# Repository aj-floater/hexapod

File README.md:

# Hexapod Robot Public Repository

## Introduction

This repository contains the public engineering artifacts for a six-legged robot project. It combines embedded firmware for RP2040-based control experiments, host-side tooling for communicating with and visualizing device state, a C++ simulation/editor shell, hardware design files, and supporting media used during development.

The public repository is organised to let a technically competent reader inspect the control stack, reproduce the host tooling, build the current simulation executable, and review the mechanical and electronics design files. It is intended as the software and hardware workspace for the project rather than a polished end-user product.

## Contextual Overview

The project is split into four main layers:

```text
hardware/ CAD and PCB assets
    ->
firmware/ RP2040 targets implementing control loops and devlink endpoints
    <-UART/devlink->
tools/devlink_dashboard/ Python host tooling for monitor, replay, commands, and GUI

software/simulation/ C++ editor-style sandbox for kinematic and UI experiments
media/ public images and videos used to illustrate development results
```

In practice, the most direct public workflow is to run a firmware target on an RP2040 board, connect it over the current devlink serial path, and inspect or record the device stream with `devlink-dashboard`.

## Repository Layout

- `firmware/`: RP2040 firmware targets, shared support code, and experimental control programs
- `tools/devlink_dashboard/`: Python package for serial monitoring, command dispatch, recording, replay, and the desktop GUI
- `software/simulation/`: Magnum-based C++ simulation/editor shell with vendored third-party dependencies
- `hardware/`: FreeCAD assemblies, KiCad projects, and board-level hardware assets
- `media/`: images and videos that illustrate assembly, calibration, and control behaviour

## Installation Instructions

### 1. Clone the repository

```bash
git clone git@github.com:aj-floater/hexapod.git
cd hexapod
```

### 2. Host tooling prerequisites

Required for `tools/devlink_dashboard/`:

- Python `>=3.11`
- `pip`
- serial support via `pyserial`
- GUI support via `PySide6` and `pyqtgraph` when using the desktop dashboard

Install the package from the repository root:

```bash
python3 -m pip install -e './tools/devlink_dashboard[gui]'
```

If you only need parser, replay, or non-GUI workflows, install the lighter serial extra instead:

```bash
python3 -m pip install -e './tools/devlink_dashboard[serial]'
```

### 3. Simulation prerequisites

Required for `software/simulation/`:

- CMake `>=3.24`
- a C++17 compiler
- a desktop OpenGL-capable environment

The simulation currently vendors its external dependencies under `software/simulation/third_party/`, so no separate package manager is required for Corrade, Magnum, SDL, ImGui, or ImGuizmo in the default workflow.

### 4. Firmware prerequisites

Required for `firmware/` work:

- Raspberry Pi Pico SDK / RP2040 toolchain
- CMake and a C/C++ compiler
- an SWD probe such as Pico Probe or a compatible CMSIS-DAP device for flashing and debugging
- UART wiring when using the current devlink path

Board-specific notes in `firmware/board.md` currently assume:

- `GP4 -> host RX`
- `GP3 -> host TX`
- shared `GND`

### 5. Hardware prerequisites

Required for `hardware/` inspection and editing:

- FreeCAD for `.FCStd` assemblies and parts
- KiCad for PCB and schematic projects

## How to Run the Software

### Host dashboard

Launch the desktop dashboard against a live serial device:

```bash
devlink-dashboard gui --port /dev/ttyACM0 --record session.jsonl
```

Other useful host workflows:

```bash
devlink-dashboard monitor --port /dev/ttyACM0 --record session.jsonl
devlink-dashboard replay session.jsonl
```

### Simulation

Configure, build, and run the current simulation shell:

```bash
cmake -S software/simulation -B software/simulation/build
cmake --build software/simulation/build
./software/simulation/build/bin/hexapod-simulation
```

### Firmware example

One simple public firmware workflow is the RP2040 blink/debug example:

```bash
cd firmware/blink_any_copy
make build
make flash
```

More advanced control targets live under `firmware/control_testing/`, `firmware/basic_control_testing/`, and related subdirectories.

## Technical Details

- The host-device protocol work is centered on `devlink`, with typed messages, NDJSON logging/replay, and capability-driven host state reconstruction in `tools/devlink_dashboard/`.
- Current firmware work targets RP2040 boards and uses a UART-based devlink transport. The public board notes document the active wiring assumptions and shared RX helper usage.
- The simulation executable is an editor-style sandbox rather than a full robot simulator. It currently focuses on a dockable viewport, scene hierarchy, gizmo manipulation, and persistence while replay and joint-domain integration remain future work.
- The simulation build intentionally vendors its major third-party dependencies under `software/simulation/third_party/` and pins them through the local CMake configuration.
- Hardware assets are maintained directly in native design formats so the repository doubles as a source tree for mechanical and PCB iteration, not only as an exported artifact store.

## Known Issues and Future Improvements

- The repository is large because it includes vendored C++ dependencies, CAD files, PCB assets, images, and captured telemetry recordings.
- Some tracked recordings and generated artifacts are large enough to trigger GitHub large-file warnings and may need Git LFS or curation later.
- The simulation scope is still limited to the editor/bootstrap phase; full replay, model import, and complete multi-joint behaviour are not finished.
- Firmware workflows are target-specific and assume local toolchain, probe, and serial environment setup rather than a single turnkey build.
- Hardware and software subsystems are evolving in parallel, so interfaces and assumptions may continue to change as the robot architecture matures.

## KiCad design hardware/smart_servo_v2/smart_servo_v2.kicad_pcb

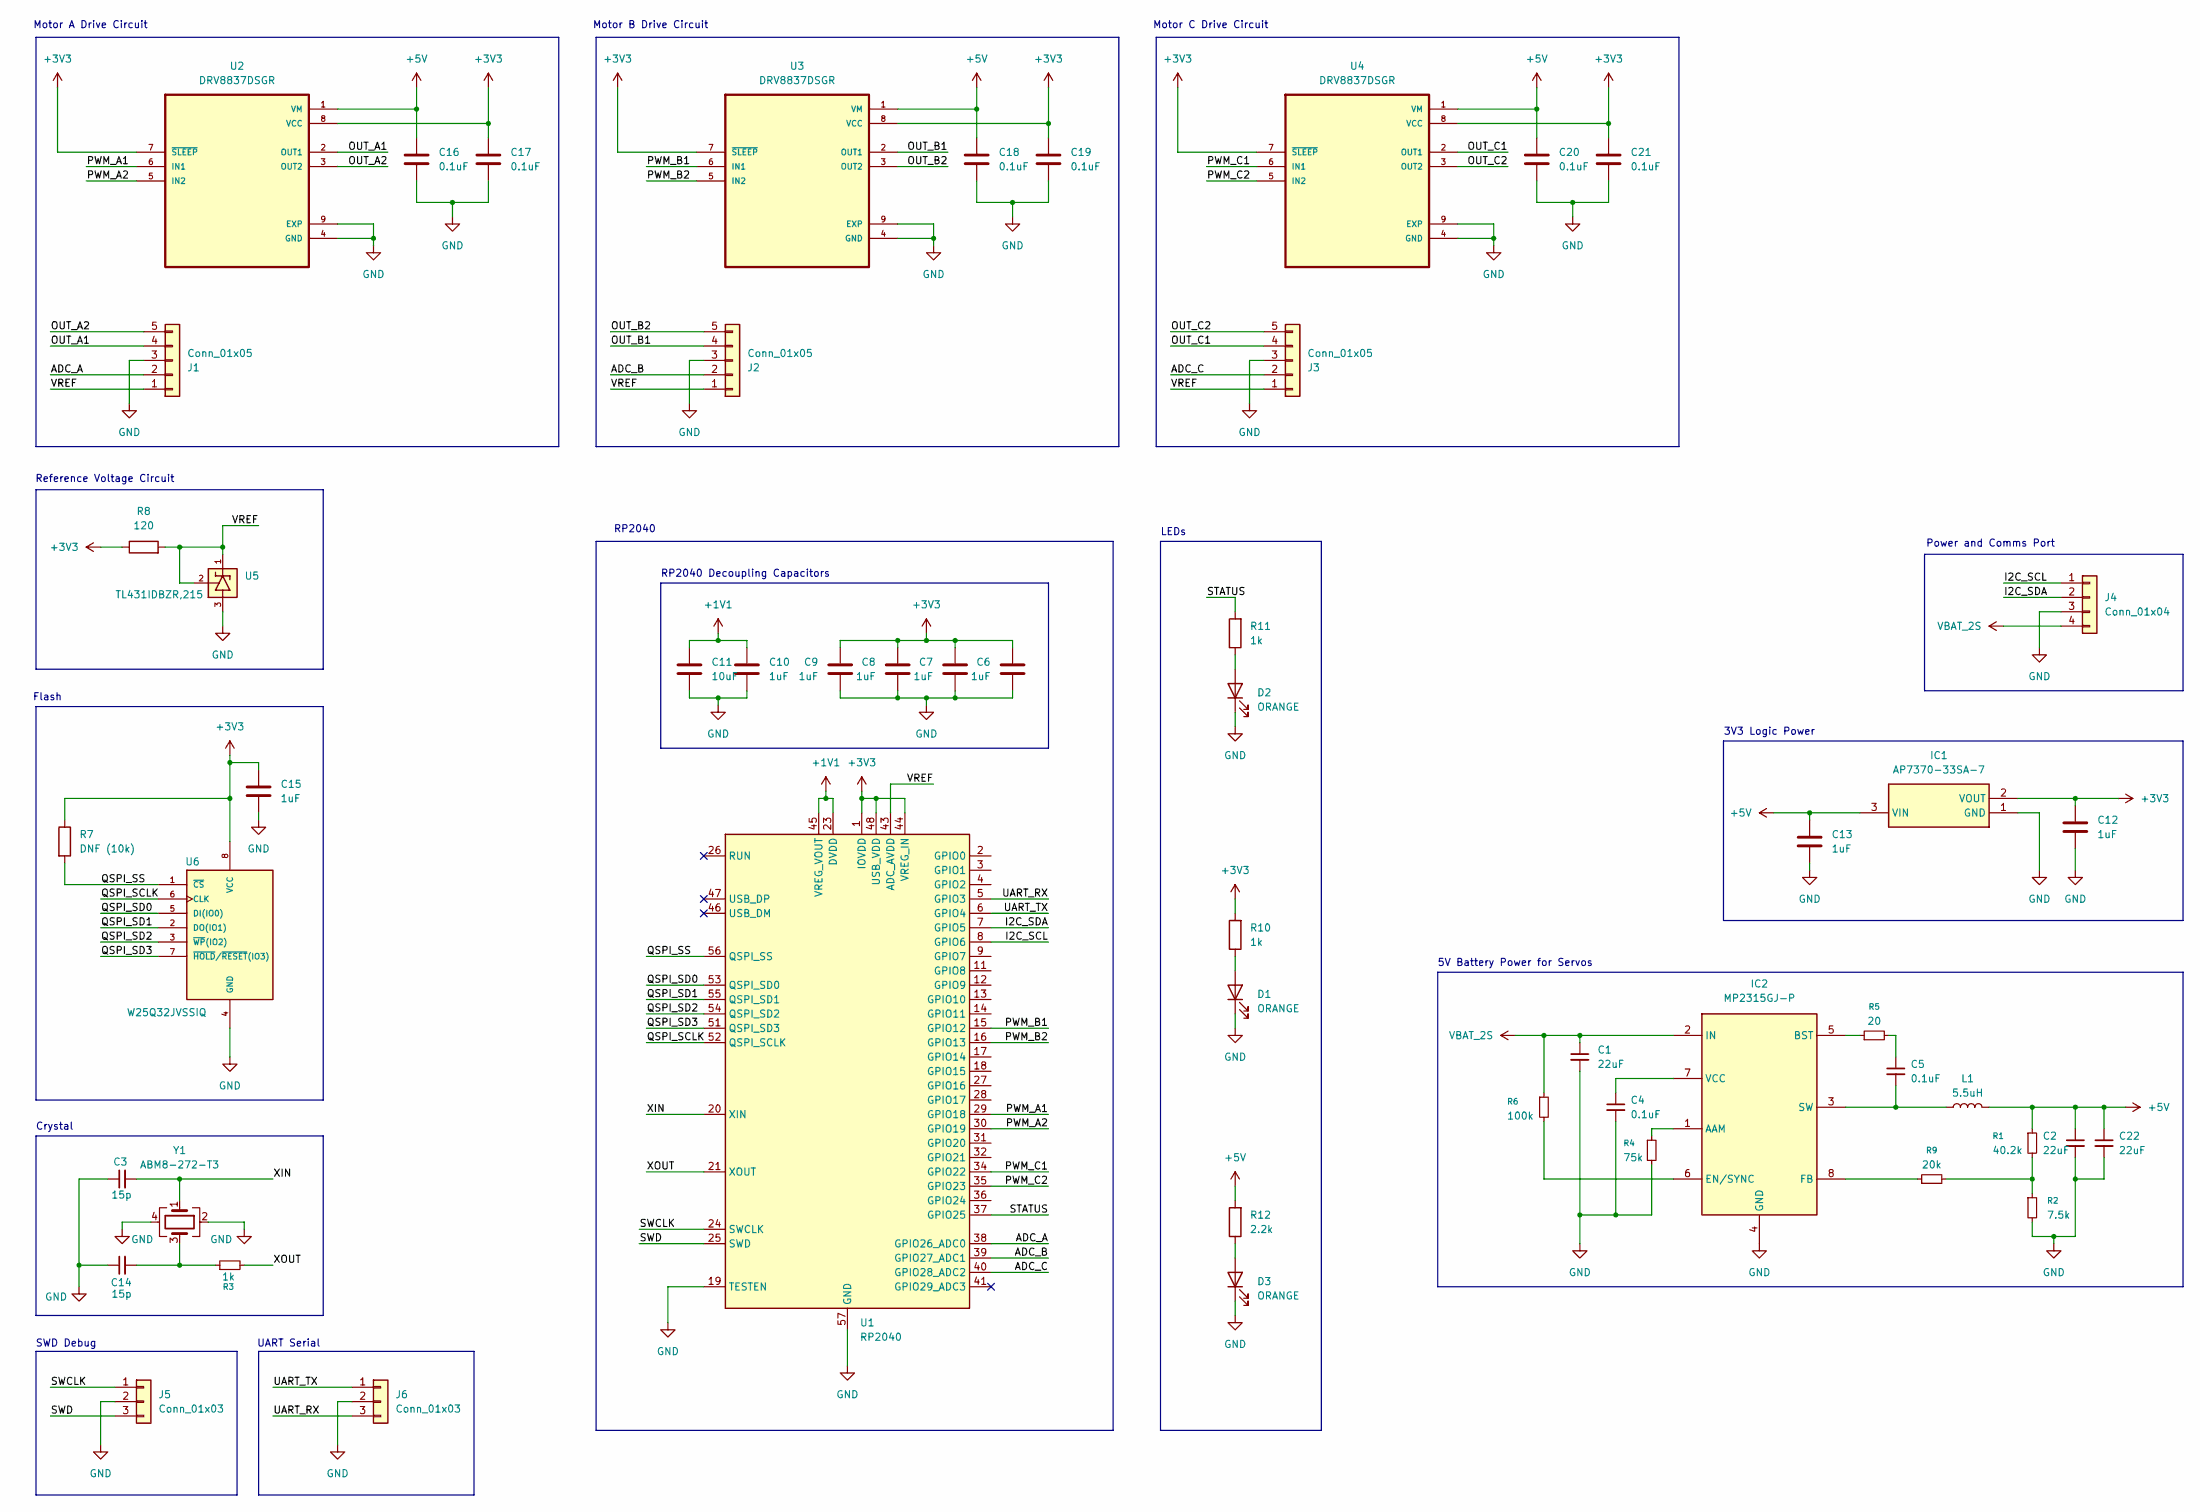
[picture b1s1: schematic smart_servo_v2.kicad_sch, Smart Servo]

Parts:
C1, C2, C22: 22uF; C_0603_1608Metric
C3, C14: 15p; C_0603_1608Metric
C4, C5, C16, C17, C18, C19, C20, C21: 0.1uF; C_0603_1608Metric
C6, C7, C8, C9, C10, C12, C13, C15: 1uF; C_0603_1608Metric
C11: 10uF; C_0603_1608Metric
D1, D2, D3: ORANGE; LED_0603_1608Metric; Manufacturer_Part_Number LO Q976.01
IC1: AP7370-33SA-7; SOT96P240X110-3N; Manufacturer_Part_Number AP7370-33SA-7
IC2: MP2315GJ-P; SOT65P280X100-8N; Manufacturer_Part_Number MP2315GJ-P
J1, J2, J3: Conn_01x05; JST_PH_B5B-PH-K_1x05_P2.00mm_Vertical
J4: Conn_01x04; JST_XH_B4B-XH-A_1x04_P2.50mm_Vertical
J5, J6: Conn_01x03; JST_PH_B3B-PH-K_1x03_P2.00mm_Vertical
L1: 5.5uH; L_Bourns_SRP7028A_7.3x6.6mm; Manufacturer_Part_Number SRP7028A-4R7M
R1: 40.2k; R_0805_2012Metric
R2: 7.5k; R_0603_1608Metric
R3, R10, R11: 1k; R_0603_1608Metric
R4: 75k; R_0805_2012Metric
R5: 20; R_0603_1608Metric
R6: 100k; R_0805_2012Metric
R7: DNF (10k); R_0805_2012Metric
R8: 120; R_0603_1608Metric
R9: 20k; R_0603_1608Metric
R12: 2.2k; R_0603_1608Metric
U1: RP2040; QFN-56-1EP_7x7mm_P0.4mm_EP3.2x3.2mm; Manufacturer_Part_Number RP2040CT
U2, U3, U4: DRV8837DSGR; SON50P200X200X80-9N; Manufacturer_Part_Number DRV8837DSGR
U5: TL431IDBZR,215; SOT95P255X145-3N; PARTREV P
U6: W25Q32JVSSIQ; SOIC127P790X216-8N; M_PART_NUMBER W25QXX
Y1: ABM8-272-T3; ABM8272T3; Manufacturer_Part_Number ABM8-272-T3

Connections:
+1V1: C10.1, C11.1, U1.23 (DVDD), U1.45 (VREG_VOUT), U1.50 (DVDD)
+3V3: C6.1, C7.1, C8.1, C9.1, C12.1, C15.1, C17.1, C19.1, C21.1, IC1.2 (VOUT), R7.1, R8.1, R10.2, U1.1 (IOVDD), U1.10 (IOVDD), U1.22 (IOVDD), U1.33 (IOVDD), U1.42 (IOVDD), U1.44 (VREG_IN), U1.48 (USB_VDD), U1.49 (IOVDD), U2.7 (~SLEEP), U2.8 (VCC), U3.7 (~SLEEP), U3.8 (VCC), U4.7 (~SLEEP), U4.8 (VCC), U6.8 (VCC)
+5V: C2.1, C13.1, C16.1, C18.1, C20.1, C22.1, IC1.3 (VIN), L1.2, R1.1, R12.2, U2.1 (VM), U3.1 (VM), U4.1 (VM)
/ADC_A: J1.2, U1.38 (GPIO26_ADC0)
/ADC_B: J2.2, U1.39 (GPIO27_ADC1)
/ADC_C: J3.2, U1.40 (GPIO28_ADC2)
/I2C_SCL: J4.1, U1.8 (GPIO6)
/I2C_SDA: J4.2, U1.7 (GPIO5)
/OUT_A1: J1.4, U2.2 (OUT1)
/OUT_A2: J1.5, U2.3 (OUT2)
/OUT_B1: J2.4, U3.2 (OUT1)
/OUT_B2: J2.5, U3.3 (OUT2)
/OUT_C1: J3.4, U4.2 (OUT1)
/OUT_C2: J3.5, U4.3 (OUT2)
/PWM_A1: U1.29 (GPIO18), U2.6 (IN1)
/PWM_A2: U1.30 (GPIO19), U2.5 (IN2)
/PWM_B1: U1.15 (GPIO12), U3.6 (IN1)
/PWM_B2: U1.16 (GPIO13), U3.5 (IN2)
/PWM_C1: U1.34 (GPIO22), U4.6 (IN1)
/PWM_C2: U1.35 (GPIO23), U4.5 (IN2)
/QSPI_SCLK: U1.52 (QSPI_SCLK), U6.6 (CLK)
/QSPI_SD0: U1.53 (QSPI_SD0), U6.5 (DI(IO0))
/QSPI_SD1: U1.55 (QSPI_SD1), U6.2 (DO(IO1))
/QSPI_SD2: U1.54 (QSPI_SD2), U6.3 (~WP(IO2))
/QSPI_SD3: U1.51 (QSPI_SD3), U6.7 (~HOLD/~RESET(IO3))
/QSPI_SS: R7.2, U1.56 (QSPI_SS), U6.1 (~CS)
/STATUS: R11.2, U1.37 (GPIO25)
/SWCLK: J5.1, U1.24 (SWCLK)
/SWD: J5.3, U1.25 (SWD)
/UART_RX: J6.3, U1.5 (GPIO3)
/UART_TX: J6.1, U1.6 (GPIO4)
/VREF: J1.1, J2.1, J3.1, R8.2, U1.43 (ADC_AVDD), U5.1, U5.2
/XIN: C3.2, U1.20 (XIN), Y1.1
/XOUT: R3.2, U1.21 (XOUT)
GND: C1.2, C2.2, C3.1, C4.2, C6.2, C7.2, C8.2, C9.2, C10.2, C11.2, C12.2, C13.2, C14.1, C15.2, C16.2, C17.2, C18.2, C19.2, C20.2, C21.2, C22.2, D1.1 (K), D2.1 (K), D3.1 (K), IC1.1 (GND), IC2.4 (GND), J1.3, J2.3, J3.3, J4.3, J5.2, J6.2, R2.2, R4.2, U1.19 (TESTEN), U1.57 (GND), U2.4 (GND), U2.9 (EXP), U3.4 (GND), U3.9 (EXP), U4.4 (GND), U4.9 (EXP), U5.3, U6.4 (GND), Y1.2, Y1.4
unnamed: C5.1, R5.2
unnamed: C14.2, R3.1, Y1.3
unnamed: D1.2 (A), R10.1
unnamed: D2.2 (A), R11.1
unnamed: D3.2 (A), R12.1
unnamed: IC2.1 (AAM), R4.1
unnamed: IC2.5 (BST), R5.1
unnamed: IC2.6 (EN/SYNC), R6.2
unnamed: IC2.8 (FB), R9.1
unnamed: C5.2, IC2.3 (SW), L1.1
unnamed: C4.1, IC2.7 (VCC)
unnamed: R1.2, R2.1, R9.2
VBAT_2S: C1.1, IC2.2 (IN), J4.4, R6.1

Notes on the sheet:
5V Battery Power for Servos
Motor B Drive Circuit
Motor C Drive Circuit
Motor A Drive Circuit
UART Serial
LEDs
Crystal
Flash
Reference Voltage Circuit
RP2040
Power and Comms Port
SWD Debug
RP2040 Decoupling Capacitors
3V3 Logic Power

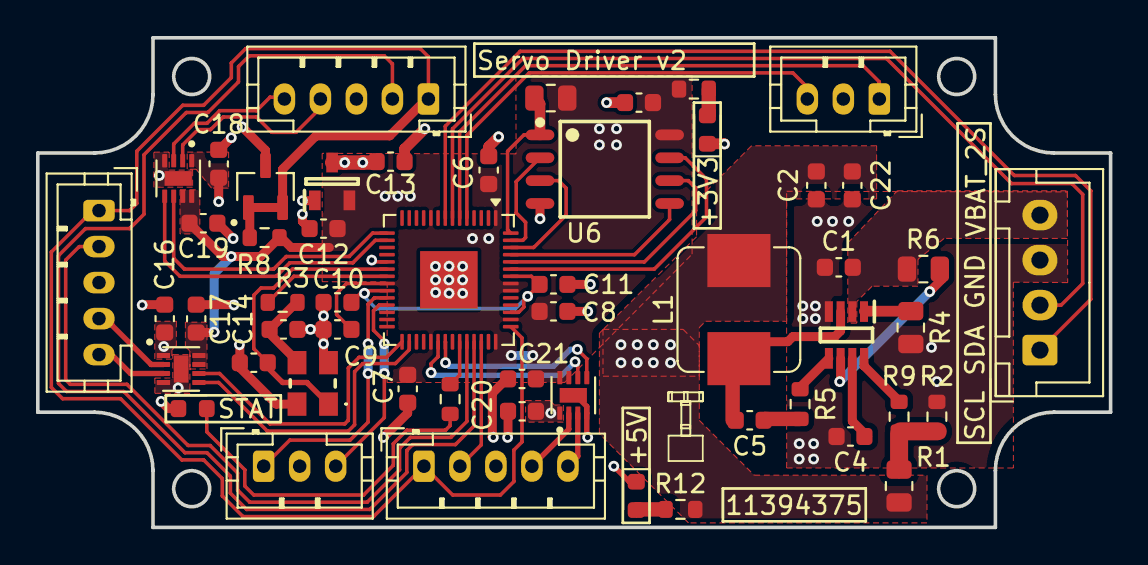
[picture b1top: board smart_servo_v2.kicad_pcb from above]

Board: 2 copper layers, 59.6 x 27.2 mm, 53 parts (0 on the bottom side), 48 nets.

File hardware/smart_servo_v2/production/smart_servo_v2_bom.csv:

Designator,Footprint,Quantity,Value,LCSC Part #
"C1, C2, C22",0603,3,22uF,
"C10, C12, C13, C15, C6, C7, C8, C9",0603,8,1uF,
C11,0603,1,10uF,
"C14, C3",0603,2,15p,
"C16, C17, C18, C19, C20, C21, C4, C5",0603,8,0.1uF,
"D1, D2, D3",0603,3,ORANGE,
IC1,SOT96P240X110-3N,1,AP7370-33SA-7,
IC2,SOT65P280X100-8N,1,MP2315GJ-P,
"J1, J2, J3",JST_PH_B5B-PH-K_1x05_P2.00mm_Vertical,3,Conn_01x05,
J4,JST_XH_B4B-XH-A_1x04_P2.50mm_Vertical,1,Conn_01x04,
"J5, J6",JST_PH_B3B-PH-K_1x03_P2.00mm_Vertical,2,Conn_01x03,
L1,L_Bourns_SRP7028A_7.3x6.6mm,1,5.5uH,
R1,0805,1,40.2k,
"R10, R11, R3",0603,3,1k,
R12,0603,1,2.2k,
R2,0603,1,7.5k,
R4,0805,1,75k,
R5,0603,1,20,
R6,0805,1,100k,
R7,0805,1,DNF (10k),
R8,0603,1,120,
R9,0603,1,20k,
U1,QFN-56-1EP_7x7mm_P0.4mm_EP3.2x3.2mm,1,RP2040,
"U2, U3, U4",SON50P200X200X80-9N,3,DRV8837DSGR,
U5,SOT95P255X145-3N,1,"TL431IDBZR,215",
U6,SOIC127P790X216-8N,1,W25Q32JVSSIQ,
Y1,ABM8272T3,1,ABM8-272-T3,

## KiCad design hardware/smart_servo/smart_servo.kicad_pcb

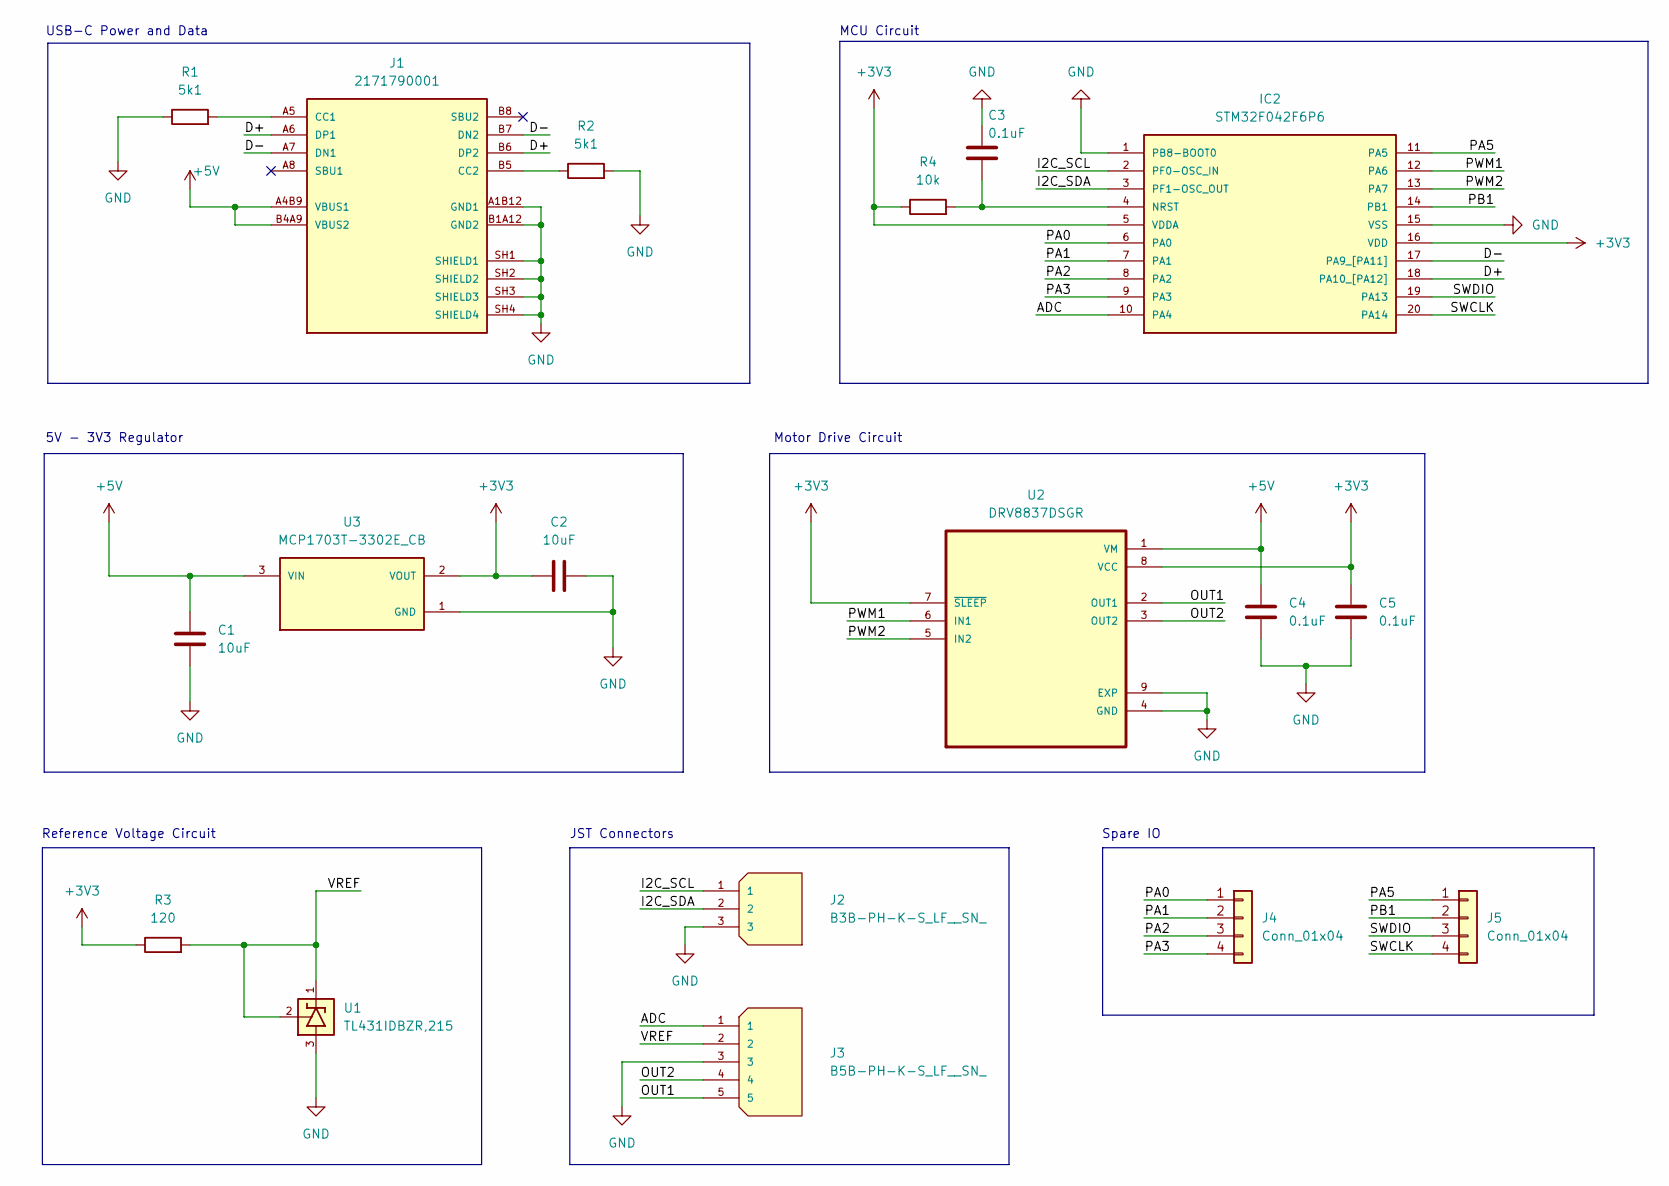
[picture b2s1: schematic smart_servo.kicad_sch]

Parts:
C1, C2: 10uF; C_0805_2012Metric
C3, C4, C5: 0.1uF; C_0402_1005Metric
IC2: STM32F042F6P6; SOP65P640X120-20N; MOUSER_PART_NUMBER 511-STM32F042F6P6
J1: 2171790001; MOLEX_2171790001; PARTREV A1
J2: B3B-PH-K-S_LF__SN_; JST_B3B-PH-K-S_LF__SN_
J3: B5B-PH-K-S_LF__SN_; JST_B5B-PH-K-S_LF__SN_
J4: Conn_01x04; PinSocket_1x04_P2.54mm_Vertical
J5: Conn_01x04; PinHeader_1x04_P2.54mm_Vertical
R1, R2: 5k1; R_0603_1608Metric
R3: 120; R_0402_1005Metric
R4: 10k; R_0402_1005Metric
U1: TL431IDBZR,215; SOT95P255X145-3N; PARTREV P
U2: DRV8837DSGR; SON50P200X200X80-9N
U3: MCP1703T-3302E_CB; SOT95P255X145-3N; PARTREV F

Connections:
+3V3: C2.2, C5.1, IC2.5 (VDDA), IC2.16 (VDD), R3.1, R4.1, U2.7 (~SLEEP), U2.8 (VCC), U3.2 (VOUT)
+5V: C1.1, C4.1, J1.A4B9 (VBUS1), J1.B4A9 (VBUS2), U2.1 (VM), U3.3 (VIN)
/ADC: IC2.10 (PA4), J3.1
/D+: IC2.18 (PA10_[PA12]), J1.A6 (DP1), J1.B6 (DP2)
/D-: IC2.17 (PA9_[PA11]), J1.A7 (DN1), J1.B7 (DN2)
/I2C_SCL: IC2.2 (PF0-OSC_IN), J2.1
/I2C_SDA: IC2.3 (PF1-OSC_OUT), J2.2
/OUT1: J3.5, U2.2 (OUT1)
/OUT2: J3.4, U2.3 (OUT2)
/PA0: IC2.6 (PA0), J4.1
/PA1: IC2.7 (PA1), J4.2
/PA2: IC2.8 (PA2), J4.3
/PA3: IC2.9 (PA3), J4.4
/PA5: IC2.11 (PA5), J5.1
/PB1: IC2.14 (PB1), J5.2
/PWM1: IC2.12 (PA6), U2.6 (IN1)
/PWM2: IC2.13 (PA7), U2.5 (IN2)
/SWCLK: IC2.20 (PA14), J5.4
/SWDIO: IC2.19 (PA13), J5.3
/VREF: J3.2, R3.2, U1.1, U1.2
GND: C1.2, C2.1, C3.1, C4.2, C5.2, IC2.1 (PB8-BOOT0), IC2.15 (VSS), J1.A1B12 (GND1), J1.B1A12 (GND2), J1.SH1 (SHIELD1), J1.SH2 (SHIELD2), J1.SH3 (SHIELD3), J1.SH4 (SHIELD4), J2.3, J3.3, R1.1, R2.2, U1.3, U2.4 (GND), U2.9 (EXP), U3.1 (GND)
unnamed: C3.2, IC2.4 (NRST), R4.2
unnamed: J1.A5 (CC1), R1.2
unnamed: J1.B5 (CC2), R2.1

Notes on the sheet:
USB-C Power and Data
Reference Voltage Circuit
Spare IO
MCU Circuit
Motor Drive Circuit
5V - 3V3 Regulator
JST Connectors

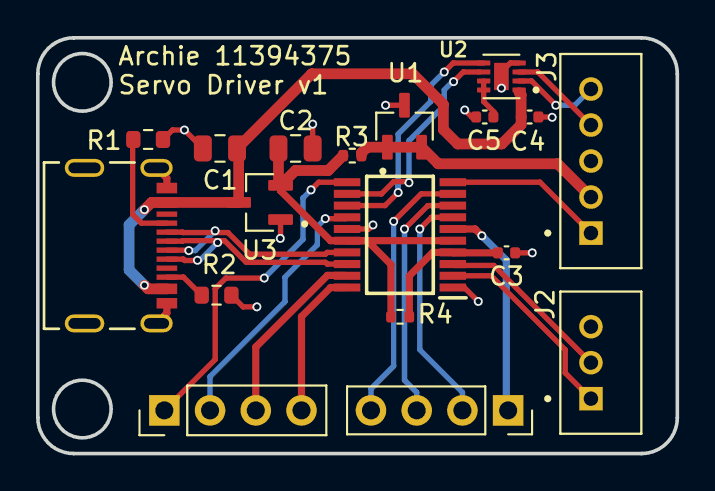
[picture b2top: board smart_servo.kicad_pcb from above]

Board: 2 copper layers, 35.5 x 23.1 mm, 18 parts (0 on the bottom side), 24 nets.

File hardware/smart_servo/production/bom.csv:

Designator,Footprint,Quantity,Value,LCSC Part #
"C1, C2",0805,2,10uF,
"C3, C4, C5",0402,3,0.1uF,
IC2,SOP65P640X120-20N,1,STM32F042F6P6,
J1,MOLEX_2171790001,1,2171790001,
J2,JST_B3B-PH-K-S_LF__SN_,1,B3B-PH-K-S_LF__SN_,
J3,JST_B5B-PH-K-S_LF__SN_,1,B5B-PH-K-S_LF__SN_,
J4,PinSocket_1x04_P2.54mm_Vertical,1,Conn_01x04,
J5,PinHeader_1x04_P2.54mm_Vertical,1,Conn_01x04,
"R1, R2",0603,2,5k1,
R3,0402,1,120,
R4,0402,1,10k,
U1,SOT95P255X145-3N,1,"TL431IDBZR,215",
U2,SON50P200X200X80-9N,1,DRV8837DSGR,
U3,SOT95P255X145-3N,1,MCP1703T-3302E_CB,

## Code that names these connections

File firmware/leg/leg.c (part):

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
static void init_adc_bank(AdcBank *bank) {
    adc_pot_system_init();
    adc_pot_init(&bank->a, "adc_a", LEG_POT_A_GPIO);
    adc_pot_init(&bank->b, "adc_b", LEG_POT_B_GPIO);
    adc_pot_init(&bank->c, "adc_c", LEG_POT_C_GPIO);
}

static void init_motor_bank(MotorBank *bank) {
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
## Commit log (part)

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2025-10-16 Add .gitignore for LaTeX auxiliary files
2025-10-16 repository for research and development of a six‑legged robot (simulation, firmware, hardware design and documentation).
2025-10-17 - project outline gantt chart good
2025-10-17 - completed project outline and uploaded
2025-10-17 - added the risk assessment
2026-02-13 Add blink_any project with GPIO25 blink firmware
2026-02-13 Add VS Code project settings for blink_any
2026-02-13 Add KiCad ESP32 demo project assets
2026-02-13 Add RP2040 minimal r2 hardware project
2026-02-13 Add rc-transmitter hardware project
2026-02-13 Add smart_servo hardware project and artifacts
2026-02-13 Add smart_servo_v2 hardware project and artifacts
2026-02-13 Move blink_any to firmware root
2026-02-13 Add leg firmware project with ADC serial plotter scaffold
2026-02-13 Refactor leg firmware into ADC/PWM modules and decoupled telemetry
2026-02-14 Refactor leg multicore telemetry and control split
2026-02-15 Refactor leg into telemetry sandbox loop
2026-02-15 blink_any: reduce default LED delay to 50ms
2026-02-15 blink_any: tidy launch.json formatting
2026-02-15 leg: switch launch profile to gdb remote target
2026-02-15 add blink_any_copy rp2040 debug sandbox
2026-02-15 blink_any_copy: fix LED default and ignore generated artifacts
2026-02-16 leg: add UART-triggered open-loop step test harness
2026-02-16 leg: add PIO UART RX on GPIO3 for command input
2026-03-12 chore: commit all changes
2026-03-28 Add hexapod serial protocol and dashboard core
2026-03-28 Rename devlink tooling and share PIO UART RX
2026-03-28 Add devlink dashboard GUI and rediscovery support
2026-03-28 Add multi-pane plot workspace to devlink dashboard
2026-03-29 Refine devlink dashboard plotting and controls
2026-03-29 Refine devlink dashboard plot interactions
2026-03-29 Improve devlink command reliability and status UI
2026-03-29 Use timestamped recording files in devlink dashboard
2026-03-29 Add devlink control_testing firmware target
2026-03-29 Add calibrated ADC streams to control testing
2026-03-30 Add selectable low-pass ADC filtering to control testing
2026-03-30 Improve control_testing angle calibration output
2026-03-30 Add manual motor control to control_testing
2026-03-30 Improve devlink dashboard plot export, parameter UI, and zoom behavior
2026-03-30 Add updated report assets, media, and devlink recordings
2026-03-30 Commit hardware updates, session logs, and ignore .directory files
2026-04-06 Refactor control_testing hold loop and add recordings
2026-04-08 Refactor control_testing into per-servo runtime
2026-04-08 Add concise function comments in control_testing
2026-04-08 Expand report draft and sync leg control assets
    Expand the dissertation/report material with new references, figures, and research notes. Update the leg firmware and dashboard tooling, and add the latest CAD, KiCad, and media assets for the leg co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
2026-04-09 CAD Changes
2026-04-09 Refine control testing modes and DevLink GUI
2026-04-13 firmware: harden devlink serial RX and standardize on 115200
    Move the shared PIO UART RX path onto IRQ-backed ring buffers, expose dropped-byte accounting, and emit protocol.rx_overflow from firmware targets when command bytes are lost. Also remove the invalid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
    Extend devlink telemetry support with stream ids and binary sample-format metadata in capabilities, emit binary sample frames from firmware, and teach the dashboard transport/parser stack to handle b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
2026-04-13 Add teach playback recording controls
2026-04-20 Add Magnum simulation editor shell
2026-04-20 Convert simulation camera to turntable
2026-04-20 Fix viewport picking and child transform inheritance
2026-04-25 Update report literature review and figures
2026-04-27 Add leg visualization tools
2026-04-27 Add fixed-B workspace sweeps
2026-04-27 docs/report snapshot before mechanical rewrite
2026-05-02 Sync non-doc firmware, hardware, simulation, and tooling updates
2026-05-02 Remove public docs history and replace repository README
